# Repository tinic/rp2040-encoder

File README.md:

# RP2040 LinuxCNC HAL Quadrature Encoder Interface

**Bridge an existing 5 V TTL DRO (Digital Read Out) — TOAUTO, Sino, Ditron, generic glass-scale kits — into LinuxCNC over USB without removing the DRO.** Think of it as *TouchDRO's spirit, but the host is LinuxCNC instead of an Android tablet*: splice into the existing DB9 cabling, keep the original DRO display working, and mirror the X/Y/Z position counts into LinuxCNC as a HAL component.

## Overview

This project connects existing DRO scales with TTL-level A/B quadrature signals to LinuxCNC through a simple USB connection. It splices into the existing DB9 connectors/cables so the original DRO continues to function. Common brands which work include [TOAUTO](https://www.toautotool.com/products/2-3-axis-dro-kit-standard-scales), Sino, Ditron, and other 5 V TTL quadrature glass-scale and magnetic-scale kits.

The hardware is intentionally minimal:

**Waveshare RP2040-Zero** — compact RP2040 board, USB-C, built-in WS2812 status LED.

**Texas Instruments ISO7760FDBQR digital isolator** — 6-channel forward, SSOP-16, default-LOW *F* variant. Provides 5 kVrms galvanic isolation between the machine-side electrical environment and the USB host PC, important on machines with VFDs, servo drives, or noisy ground references. See [`hardware/README.md`](hardware/README.md) for the full pinout and a startup-glitch caveat tied to the F suffix.

## Finished board

Spliced into the existing DRO via DB9 breakouts — there are likely nicer-looking solutions than this:

## Features

- 3 DRO scales (X, Y, Z) with TTL A/B quadrature signals; firmware supports a 4th channel if hardware is extended
- PIO-based edge counting on the RP2040 — no software polling loop, no missed transitions
- DMA reload pair per channel drains the PIO RX FIFO into memory with **zero CPU involvement**, so position counts cannot drop regardless of scale velocity
- 32-bit signed position counters per axis
- Optional reference (R / index) pulse input per axis: pulse count, the position latched at the pulse, and LinuxCNC's index handshake, as HAL pins
- USB vendor-class device + LinuxCNC HAL userspace component
- Configurable per-axis scale factors (compile-time defaults overridable at runtime over USB or via HAL pins)
- Built-in test mode (sine / circular / linear / random) for development and debugging without scales attached
- Hardware watchdog: automatic reboot + USB re-enumeration on firmware hang
- 5 kVrms galvanic isolation between machine and host PC

## Quick Start

See the individual directories for detailed instructions:
- [`rp2040-firmware/`](rp2040-firmware/) — RP2040 firmware (Pico SDK 2.2.0, C++23)
- [`linuxcnc-hal/`](linuxcnc-hal/) — LinuxCNC HAL component (`halcompile --install`)
- [`hardware/`](hardware/) — Hardware setup, isolator wiring, and DB9 splice diagrams

## How this compares to other projects

The DIY DRO and LinuxCNC encoder-interface space has a few well-known projects; this one occupies a specific niche.

| Project | Host | Connection | Goal |
|---------|------|------------|------|
| **This project** | LinuxCNC | USB | Mirror an existing DRO into LinuxCNC as position feedback, preserve the original display |
| [TouchDRO (Yuriy Krushelnytskiy)](https://www.touchdro.com/resources/adapters/diy/) | Android / Fire tablet | Bluetooth | Replace a physical DRO display with a tablet UI |
| [atrex66/stepper-ninja](https://github.com/atrex66/stepper-ninja) | LinuxCNC | UDP / Ethernet | RP2040 as a deterministic motion controller (step generation + encoder feedback) |
| [Remora](https://github.com/scottalford75/Remora) | LinuxCNC on RPi | SPI | STM32/LPC176x as a realtime co-processor for motion |
| [Mesa hostmot2 cards](https://linuxcnc.org/docs/html/man/man9/hostmot2.9.html) | LinuxCNC | PCI / Ethernet | FPGA-based deterministic motion + encoder, commercial gold standard |
| [adamgreen/QuadratureDecoder](https://github.com/adamgreen/QuadratureDecoder) | (library only) | — | PIO+DMA RP2040 quadrature library; no USB/CNC integration |

**Why USB and not Ethernet?** USB is non-deterministic by design and is the wrong tool for LinuxCNC's realtime motion loop. It's the right tool for **position display / DRO mirroring**, where missing a single millisecond update doesn't matter and only the integral count needs to be correct — which is exactly what this project does. If you need closed-loop motion feedback for servoing, look at Mesa, Remora, or stepper-ninja.

**Why an isolator rather than a level shifter?** Glass-scale cables run through the machine alongside power and motor wiring. Galvanic isolation between the machine ground and the host PC's USB ground avoids ground loops, VFD/servo noise injection, and reduces the blast radius of a wiring fault. The earlier revision of this project used a TXS0108E bidirectional level shifter; the current design uses an ISO7760FDBQR digital isolator.

## Keywords

LinuxCNC, DRO, digital readout, glass scale, magnetic scale, quadrature encoder, TTL, 5V TTL, RP2040, Raspberry Pi Pico, ISO7760, digital isolator, galvanic isolation, USB, HAL component, TOAUTO, Sino, Ditron, CNC, milling machine, lathe, retrofit, splice, position feedback, TouchDRO alternative.

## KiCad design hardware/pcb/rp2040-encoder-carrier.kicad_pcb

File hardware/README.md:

# Hardware Setup - RP2040 Quadrature Encoder Interface

This document describes the hardware setup for the RP2040-based USB
quadrature encoder interface for LinuxCNC DRO (Digital Readout) systems.

## Overview

The system reads 3 quadrature encoders (X, Y, Z) and reports position
over USB to LinuxCNC. PIO state machines on the RP2040 do the edge
counting; a DMA reload pair per channel drains the PIO RX FIFOs into
memory with zero CPU involvement. Encoder signals cross a 5 kVrms
galvanic isolation barrier (ISO7760FDBQR) before reaching the RP2040
GPIOs, protecting the USB host from machine-side electrical events.

The firmware also supports a 4th encoder channel on GPIO 6/7 (rotary
A-axis), but that channel is **not** wired through on the isolation
board described here — the ISO7760FDBQR has exactly 6 forward channels,
fully consumed by 3 axes × 2 quadrature lines. GPIO 6 and GPIO 7 are
tied to GND on the board so the 4th PIO state machine sees a stable
`00` input and reports a fixed zero position; no phantom counts.

## Required Components

| Component | Notes |
|-----------|-------|
| **Waveshare RP2040 Zero** | Compact RP2040 board with built-in WS2812 RGB status LED |
| **ISO7760FDBQR** | TI 6-channel forward digital isolator, SSOP-16, default-LOW (the *F* suffix) |
| 10-pin 2.54 mm PCB terminal block | Encoder cable terminations |
| Glass scales / TTL quadrature encoders | 5 V A/B signals |
| TOAUTO DRO (optional) | Original DRO; can run in parallel via DB9 taps |
| Jienk DB9 M/F breakout boards | One per axis, used to tap scale signals without cutting cables |

### Connection Strategy

The existing glass scale ↔ TOAUTO DRO link is intercepted with DB9
breakout boards. A/B signals branch off to the terminal block on the
RP2040 enclosure; the scales stay wired to the DRO so the original
display continues to work. The ISO7760FDBQR sits in the RP2040 enclosure
and isolates the machine's electrical environment from the USB host PC.

## Pin Assignments

### Quadrature Encoder Inputs

| Encoder | Axis | RP2040 GPIO | ISO7760F output | ISO7760F input | Terminal |
|---------|------|-------------|-----------------|----------------|----------|
| 0       | X    | GPIO 0 (A)  | OUTA (pin 15)   | INA (pin 2)    | A        |
| 0       | X    | GPIO 1 (B)  | OUTB (pin 14)   | INB (pin 3)    | B        |
| 1       | Y    | GPIO 2 (A)  | OUTC (pin 13)   | INC (pin 4)    | A        |
| 1       | Y    | GPIO 3 (B)  | OUTD (pin 12)   | IND (pin 5)    | B        |
| 2       | Z    | GPIO 4 (A)  | OUTE (pin 11)   | INE (pin 6)    | A        |
| 2       | Z    | GPIO 5 (B)  | OUTF (pin 10)   | INF (pin 7)    | B        |

### Optional Reference (R / Index) Pulse Inputs

Glass scales with a reference/index track (e.g. 50 mm periodic marks on Sino/Ditron/TOAUTO scales, typically DB9 pin 8) can be connected to **GP26–GP29** (on the right-side header of the RP2040-Zero, next to `3V3`/`GND`):

| Encoder | Axis | RP2040 GPIO | Signal | Notes |
|---------|------|-------------|--------|-------|
| 0       | X    | GPIO 26     | R (Index) | Enabled by default; internal pull-down keeps unwired pins quiet |
| 1       | Y    | GPIO 27     | R (Index) | Enabled by default; internal pull-down keeps unwired pins quiet |
| 2       | Z    | GPIO 28     | R (Index) | Enabled by default; internal pull-down keeps unwired pins quiet |
| 3       | A    | GPIO 29     | R (Index) | Enabled by default; internal pull-down keeps unwired pins quiet |

Not every scale has periodic marks. The three scales of one Grizzly G0759 retrofit each give exactly one pulse over their whole travel (404, 140 and 262 mm). To find out what a scale gives, watch `rp2040-encoder.0.ref-count-N` and `ref-position-N` while moving the axis from one end to the other; the HAL pins are described in [`../linuxcnc-hal/README.md`](../linuxcnc-hal/README.md).

Because the primary `ISO7760FDBQR` consumes all 6 channels for X/Y/Z A+B, wire R signals through an additional 3.3 V-output isolator (such as an `ISO7740F` for 4 channels) — never feed 5 V directly into GP26–GP29. When unused, leave GP26–GP29 disconnected; internal pull-downs prevent floating interrupts and main position counting is unaffected unless `index-enable-N` is armed.

Power and ground:

| ISO7760F pin | Net          | Notes                          |
|--------------|--------------|--------------------------------|
| VCC1 (pin 1) | +5 V         | Encoder side, from DRO supply  |
| GND1 (pin 8) | Machine GND  | Encoder side                   |
| VCC2 (pin 16)| +3.3 V       | RP2040 side, from `3V3` pin    |
| GND2 (pin 9) | RP2040 GND   | RP2040 side                    |

Decoupling: 0.1 µF from VCC1→GND1 and VCC2→GND2, placed close to the
package.

## ISO7760FDBQR Setup

The ISO7760FDBQR is a **unidirectional** 6-channel digital isolator: all
6 channels go INA-F → OUTA-F. The encoder side must be wired to the
**input pins** (pins 2–7), and the RP2040 side to the **output pins**
(pins 10–15). Reversing this will not work — there is no auto-direction
detection like the older parts.

### Default-LOW behavior (the *F* suffix)

The `F` in `ISO7760FDBQR` is load-bearing:

- **With F (this part)**: outputs go **LOW** when the input pin is
  floating, when VCC1 is unpowered, or when the input cable is
  disconnected.
- **Without F**: outputs would go **HIGH** in the same conditions.

This matters at startup and during scale disconnect events. If the
scales are unpowered or their cables aren't yet biased while the RP2040
side is alive, the RP2040 sees `A=0, B=0` on every channel. When the
scales come up at their true logic levels (often `A=0, B=1` or `A=1,
B=0`), the PIO observes a `00 → 01` or `00 → 10` transition and records
a **spurious ±1 count** before any real motion has occurred. The same
happens in reverse on power-down.

Mitigation: zero the affected axes from LinuxCNC after every full
power-up cycle, or sequence scale power and USB connect so that the
scales are biased before the RP2040 enumerates. Verify you have the
**F variant** physically — the standard ISO7760 (no F) inverts this
behavior and produces opposite-polarity startup glitches.

### Why no internal pulls

The ISO7760F outputs are CMOS push-pull (~20 Ω driver, ±15 mA absolute
max), strong enough to drive RP2040 GPIO inputs directly with no
external resistors. The firmware leaves the RP2040 internal pulls
disabled (`gpio_set_pulls(pin, false, false)` in
`quadrature_encoder.pio`).

If your encoders are **open-collector / open-drain** rather than
push-pull TTL, add 1–10 kΩ pull-ups to +5 V on the **input side** of the
ISO7760F (between the terminal block and pins 2–7). Most modern TTL
scales are push-pull and don't need this.

## TOAUTO DRO Integration

### DB9 Pinout (per axis)

| Pin | Signal | Description           |
|-----|--------|-----------------------|
| 1   | +5 V   | Power supply          |
| 2   | 0 V    | Ground                |
| 3   | A      | Quadrature A (TTL)    |
| 4   | B      | Quadrature B (TTL)    |
| 5–9 | NC     | Not connected         |

### Per-axis wiring

For each of X, Y, Z:

1. Use a Jienk DB9 male/female breakout board.
2. Glass scale → Female DB9.
3. TOAUTO DRO → Male DB9.
4. Tap pins 3 (A) and 4 (B) at the breakout to the RP2040 enclosure
   terminal block.
5. Tie all DB9 pin-2 grounds to the ISO7760F GND1 net.
6. Tie all DB9 pin-1 +5 V together as the VCC1 net (also powers the
   isolator's encoder side).

## Encoder Specifications

| Property          | Value                                          |
|-------------------|------------------------------------------------|
| Voltage levels    | 5 V TTL (isolated to 3.3 V across the barrier) |
| Signal type       | Single-ended A/B quadrature                    |
| Max edge rate     | ≪ 100 Mbps isolator limit; PIO sample rate ≫ any realistic encoder |
| Channels per axis | 2 (A and B); index/Z not used                  |

## Assembly Steps

1. Flash the firmware (see `rp2040-firmware/README.md`).
2. Hand-wire the ISO7760FDBQR to the RP2040 Zero per the pin table
   above. Decoupling caps as close to VCC1/VCC2 as practical.
3. Wire the terminal block to the ISO7760F input side (pins 2–7) and to
   the VCC1 / GND1 nets.
4. Wire the DB9 breakouts and connect glass scale ↔ DRO through them,
   tapping A/B/+5/GND off to the terminal block.
5. Power the DRO, then connect USB to the host PC.
6. Confirm enumeration as VID:PID `2e8a:c0de`.
7. Run `test_usb_device.py` to verify counts respond to scale movement.

### Build photos

RP2040-Zero with the ISO7760F hand-wired alongside, feeding the terminal
block:

Assembled enclosure with three DB9 axis breakouts:

Installed in the machine, tapping the existing scale ↔ DRO cables:

## Troubleshooting

### No counts on any axis
- Confirm VCC1 (5 V) and VCC2 (3.3 V) are both present, with GND1/GND2
  tied to their respective ground references.
- Verify the ISO7760F is the **F suffix** part (or note the inverted
  default behavior described above).
- Check the DB9 → terminal block A/B wiring matches the table; ISO7760F
  input pins are 2–7, output pins are 15–10 (mirrored).

### Counts drift after scale power cycle
- Expected — see the default-LOW startup-glitch note above. Zero the
  affected axis in LinuxCNC after power events.

### Counts in wrong direction
- Swap A and B at the terminal block, **or** set a negative scale factor
  from the host (USB `SET_SCALE` command / HAL `scale-N` pin).

### Erratic counts with no motion
- Most likely an open-collector encoder without a pull-up on the input
  side. Add 1–10 kΩ pull-ups to +5 V on the affected channels.
- Check the scale cable shield is grounded only at one end.

### DRO continues to work but USB doesn't
- Verify the ISO7760F output side is wired to the **RP2040** (pins
  15–10 → GPIOs 0–5), not the encoder side. The chip is unidirectional;
  swapping breaks it.

### USB enumerates but reads fail
- Check `dmesg` for libusb permission errors; a udev rule for VID 2e8a
  PID c0de may be required.

## Configuration

Scale factors are configured in `rp2040-firmware/main.cpp` and overridable
at runtime via the LinuxCNC HAL `scale-N` pins:

```cpp
pos.set_scale(0, 0.001);  // X: 0.001 mm/count (1000 counts/mm)
pos.set_scale(1, 0.001);  // Y: 0.001 mm/count
pos.set_scale(2, 0.001);  // Z: 0.001 mm/count
pos.set_scale(3, 0.1);    // A: 0.1 deg/count — unused on this board
```

Common defaults:
- Glass scales: 0.001 mm/count (1 µm resolution)
- Rotary encoders: 360 / (PPR × 4) deg/count

## Safety

- Power off everything before changing wiring.
- The ISO7760F provides 5 kVrms isolation; do not bypass it by tying
  GND1 and GND2 together.
- Use proper enclosures and ESD handling.

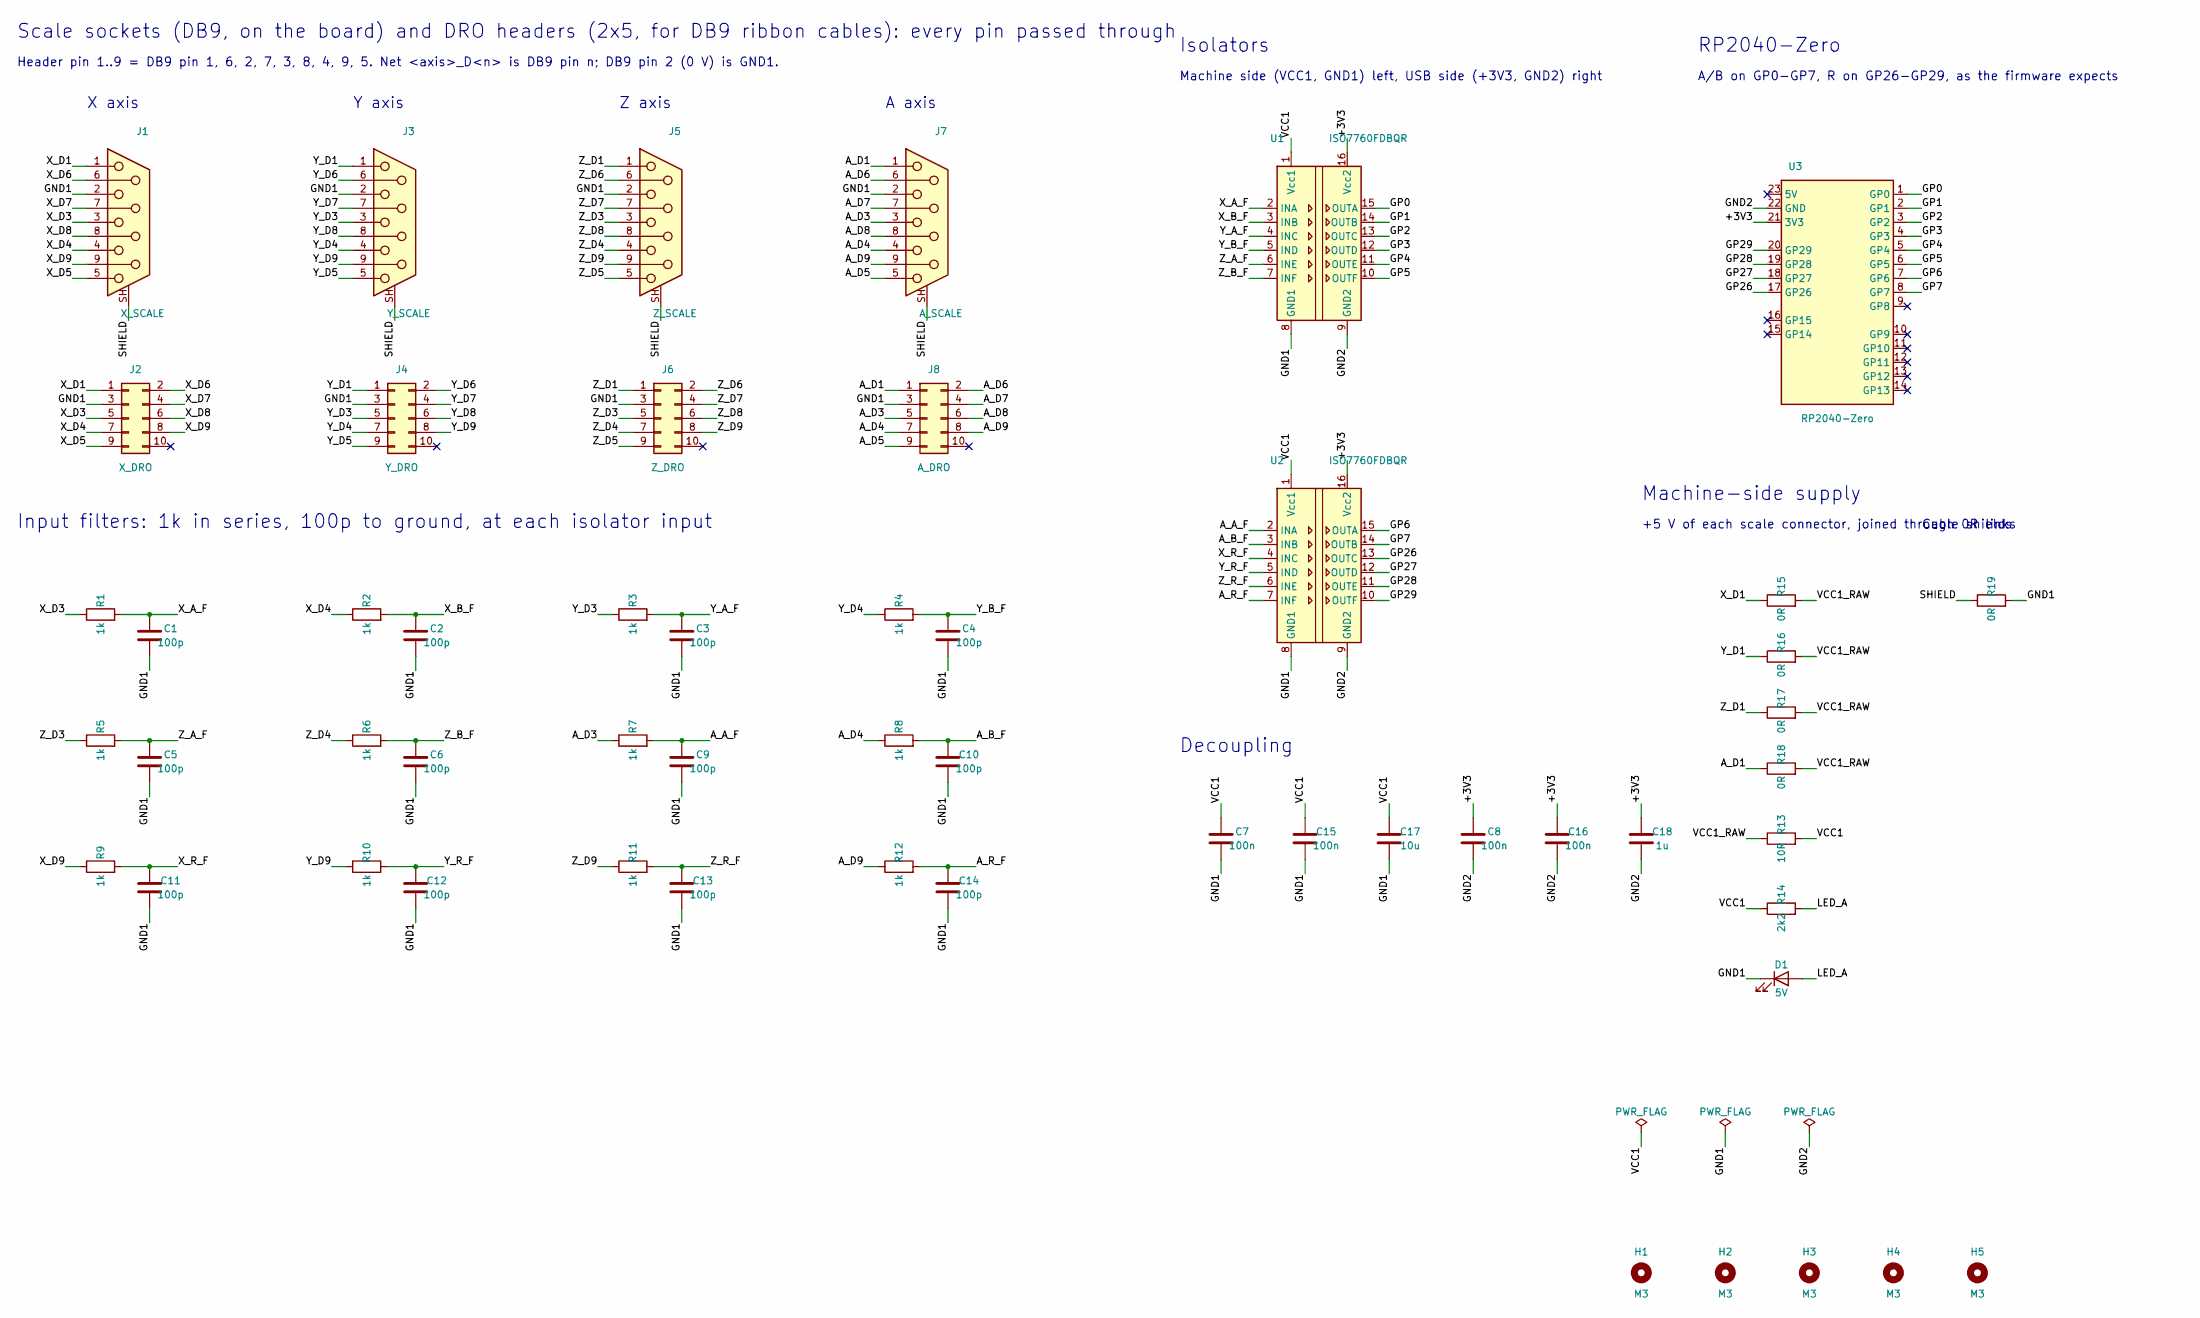
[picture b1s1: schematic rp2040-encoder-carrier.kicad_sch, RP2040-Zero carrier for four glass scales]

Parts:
C1, C2, C3, C4, C5, C6, C9, C10, C11, C12, C13, C14: 100p; C_0603_1608Metric
C7, C8, C15, C16: 100n; C_0603_1608Metric
C17: 10u; C_0805_2012Metric
C18: 1u; C_0805_2012Metric
D1: 5V; LED_0603_1608Metric
H1, H2, H3, H4, H5: M3; MountingHole_3.2mm_M3
J1: X_SCALE; DSUB-9_Socket_Vertical_Amphenol_LD09S24A4
J2: X_DRO; IDC-Header_2x05_P2.54mm_Vertical
J3: Y_SCALE; DSUB-9_Socket_Vertical_Amphenol_LD09S24A4
J4: Y_DRO; IDC-Header_2x05_P2.54mm_Vertical
J5: Z_SCALE; DSUB-9_Socket_Vertical_Amphenol_LD09S24A4
J6: Z_DRO; IDC-Header_2x05_P2.54mm_Vertical
J7: A_SCALE; DSUB-9_Socket_Vertical_Amphenol_LD09S24A4
J8: A_DRO; IDC-Header_2x05_P2.54mm_Vertical
R1, R2, R3, R4, R5, R6, R7, R8, R9, R10, R11, R12: 1k; R_0603_1608Metric
R13: 10R; R_0603_1608Metric
R14: 2k2; R_0603_1608Metric
R15, R16, R17, R18, R19: 0R; R_0603_1608Metric
U1, U2: ISO7760FDBQR; QSOP-16_3.9x4.9mm_P0.635mm
U3: RP2040-Zero

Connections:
/+3V3: C8.1, C16.1, C18.1, U1.16 (Vcc2), U2.16 (Vcc2), U3.21 (3V3)
/A_A_F: C9.1, R7.2, U2.2 (INA)
/A_B_F: C10.1, R8.2, U2.3 (INB)
/A_D1: J7.1, J8.1, R18.1
/A_D3: J7.3, J8.5, R7.1
/A_D4: J7.4, J8.7, R8.1
/A_D5: J7.5, J8.9
/A_D6: J7.6, J8.2
/A_D7: J7.7, J8.4
/A_D8: J7.8, J8.6
/A_D9: J7.9, J8.8, R12.1
/A_R_F: C14.1, R12.2, U2.7 (INF)
/GND1: C1.2, C2.2, C3.2, C4.2, C5.2, C6.2, C7.2, C9.2, C10.2, C11.2, C12.2, C13.2, C14.2, C15.2, C17.2, D1.1 (K), J1.2, J2.3, J3.2, J4.3, J5.2, J6.3, J7.2, J8.3, R19.2, U1.8 (GND1), U2.8 (GND1)
/GND2: C8.2, C16.2, C18.2, U1.9 (GND2), U2.9 (GND2), U3.22 (GND)
/GP0: U1.15 (OUTA), U3.1 (GP0)
/GP1: U1.14 (OUTB), U3.2 (GP1)
/GP2: U1.13 (OUTC), U3.3 (GP2)
/GP3: U1.12 (OUTD), U3.4 (GP3)
/GP4: U1.11 (OUTE), U3.5 (GP4)
/GP5: U1.10 (OUTF), U3.6 (GP5)
/GP6: U2.15 (OUTA), U3.7 (GP6)
/GP7: U2.14 (OUTB), U3.8 (GP7)
/GP26: U2.13 (OUTC), U3.17 (GP26)
/GP27: U2.12 (OUTD), U3.18 (GP27)
/GP28: U2.11 (OUTE), U3.19 (GP28)
/GP29: U2.10 (OUTF), U3.20 (GP29)
/LED_A: D1.2 (A), R14.2
/SHIELD: J1.SH (PAD), J3.SH (PAD), J5.SH (PAD), J7.SH (PAD), R19.1
/VCC1: C7.1, C15.1, C17.1, R13.2, R14.1, U1.1 (Vcc1), U2.1 (Vcc1)
/VCC1_RAW: R13.1, R15.2, R16.2, R17.2, R18.2
/X_A_F: C1.1, R1.2, U1.2 (INA)
/X_B_F: C2.1, R2.2, U1.3 (INB)
/X_D1: J1.1, J2.1, R15.1
/X_D3: J1.3, J2.5, R1.1
/X_D4: J1.4, J2.7, R2.1
/X_D5: J1.5, J2.9
/X_D6: J1.6, J2.2
/X_D7: J1.7, J2.4
/X_D8: J1.8, J2.6
/X_D9: J1.9, J2.8, R9.1
/X_R_F: C11.1, R9.2, U2.4 (INC)
/Y_A_F: C3.1, R3.2, U1.4 (INC)
/Y_B_F: C4.1, R4.2, U1.5 (IND)
/Y_D1: J3.1, J4.1, R16.1
/Y_D3: J3.3, J4.5, R3.1
/Y_D4: J3.4, J4.7, R4.1
/Y_D5: J3.5, J4.9
/Y_D6: J3.6, J4.2
/Y_D7: J3.7, J4.4
/Y_D8: J3.8, J4.6
/Y_D9: J3.9, J4.8, R10.1
/Y_R_F: C12.1, R10.2, U2.5 (IND)
/Z_A_F: C5.1, R5.2, U1.6 (INE)
/Z_B_F: C6.1, R6.2, U1.7 (INF)
/Z_D1: J5.1, J6.1, R17.1
/Z_D3: J5.3, J6.5, R5.1
/Z_D4: J5.4, J6.7, R6.1
/Z_D5: J5.5, J6.9
/Z_D6: J5.6, J6.2
/Z_D7: J5.7, J6.4
/Z_D8: J5.8, J6.6
/Z_D9: J5.9, J6.8, R11.1
/Z_R_F: C13.1, R11.2, U2.6 (INE)

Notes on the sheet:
Scale sockets (DB9, on the board) and DRO headers (2x5, for DB9 ribbon cables): every pin passed through
Header pin 1..9 = DB9 pin 1, 6, 2, 7, 3, 8, 4, 9, 5. Net <axis>_D<n> is DB9 pin n; DB9 pin 2 (0 V) is GND1.
X axis
Y axis
Z axis
A axis
Input filters: 1k in series, 100p to ground, at each isolator input
Isolators
Machine side (VCC1, GND1) left, USB side (+3V3, GND2) right
Decoupling
RP2040-Zero
A/B on GP0-GP7, R on GP26-GP29, as the firmware expects
Machine-side supply
+5 V of each scale connector, joined through 0R links
Cable shields

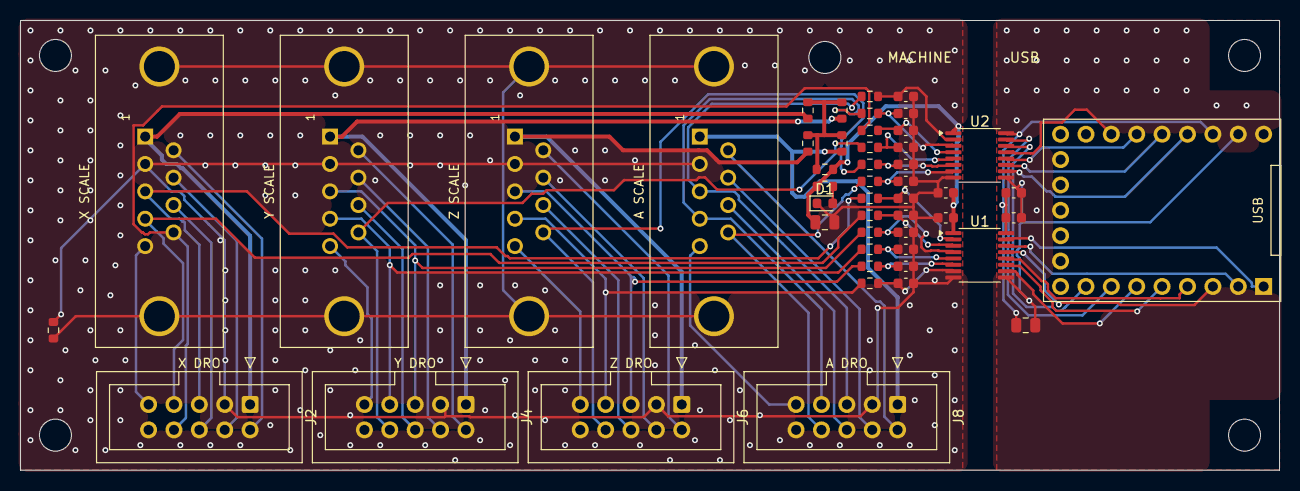
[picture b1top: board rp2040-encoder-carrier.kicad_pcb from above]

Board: 2 copper layers, 126.0 x 45.0 mm, 54 parts (0 on the bottom side), 63 nets.
